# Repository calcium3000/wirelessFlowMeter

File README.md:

# wirelessFlowMeter
This project is currently in development.  Check back soon!  But not too soon.

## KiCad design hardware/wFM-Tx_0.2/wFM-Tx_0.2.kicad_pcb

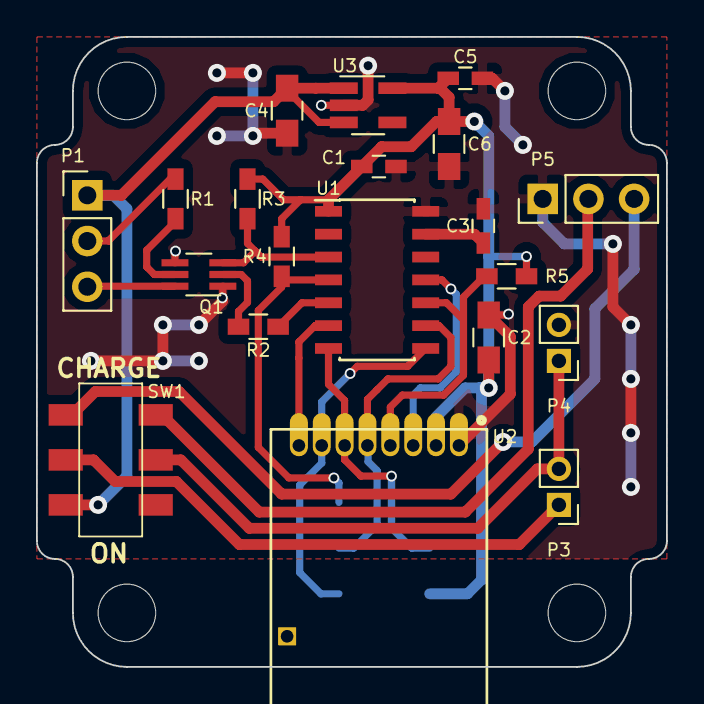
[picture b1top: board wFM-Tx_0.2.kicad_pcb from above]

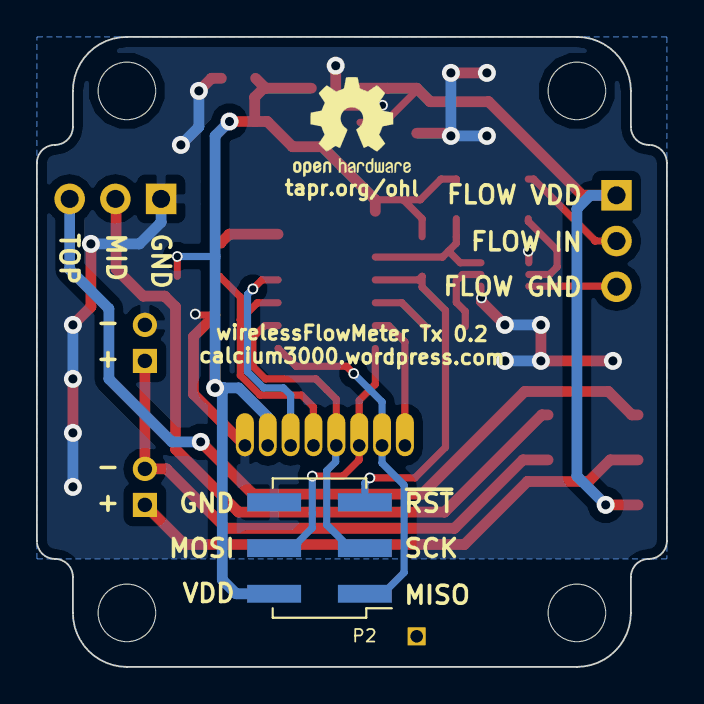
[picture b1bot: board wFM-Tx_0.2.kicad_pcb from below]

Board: 2 copper layers, 35.0 x 35.0 mm, 26 parts (2 on the bottom side), 21 nets.

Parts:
C1, C3, C5: 0.1uF; C_0603_HandSoldering
C2, C4, C6: 4.7uF; C_0805_HandSoldering
MH0, MH1, MH2, MH3: MountingHole_3.2mm_M3_ISO7380
P1, P5: 1x3; Socket_Strip_Straight_1x03_Pitch2.54mm
P2: 2x3; Socket_Strip_Straight_2x03_Pitch2.54mm_SMD
P3, P4: 1x2; S2B-PH-K-S
Q1: MBT3904DW1T1G; SOT-363_SC-70-6_Handsoldering
R1, R2, R3, R4, R5: 10k; R_0603_HandSoldering
SW1: CL-SB-22B-11T; CL-SB-12B-11T_DPDT
SYM0: OSHW-Logo2_7.3x6mm_SilkScreen
U1: ATtiny441-SSU; SOIC-14_3.9x8.7mm_Pitch1.27mm
U2: nRF24L01+_module; nRF24L01p_mini_TH
U3: MIC5205-3.0; SOT-23-5_HandSoldering

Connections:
+VDD: C1.1, C2.1, C5.1, C6.1, P2.2, R3.1, R4.1, R5.1, U1.1, U2.2, U3.5
/FLOW_GND_BASE: Q1.2, R2.1
/FLOW_IN_BASE: Q1.5, R1.1
/TINY_AREF: C3.1, U1.13
BATT_MID: P3.2, P4.1, SW1.5
BATT_POS: P3.1, SW1.2
CHRG_MID: P5.2, SW1.4
CHRG_POS: P5.3, SW1.1
FLOW_GND: P1.3, Q1.6
FLOW_GND_BR: R2.2, U1.5
FLOW_IN_BR: P1.2, R1.2
FLOW_PULSE: Q1.3, R3.2, U1.3
GND: C1.2, C2.2, C3.2, C4.2, C5.2, C6.2, P2.6, P4.2, P5.1, Q1.1, Q1.4, U1.14, U2.1, U3.2
NRF_CE: U1.11, U2.3
NRF_~CS: R5.2, U1.10, U2.4
NRF_~IRQ: U1.6, U2.8
SPI_MISO: P2.1, U1.8, U2.7
SPI_MOSI: P2.4, U1.7, U2.6
SPI_SCK: P2.3, U1.9, U2.5
TINY_~RST: P2.5, R4.2, U1.4
VBATT_2S: C4.1, P1.1, SW1.3, U3.1, U3.3

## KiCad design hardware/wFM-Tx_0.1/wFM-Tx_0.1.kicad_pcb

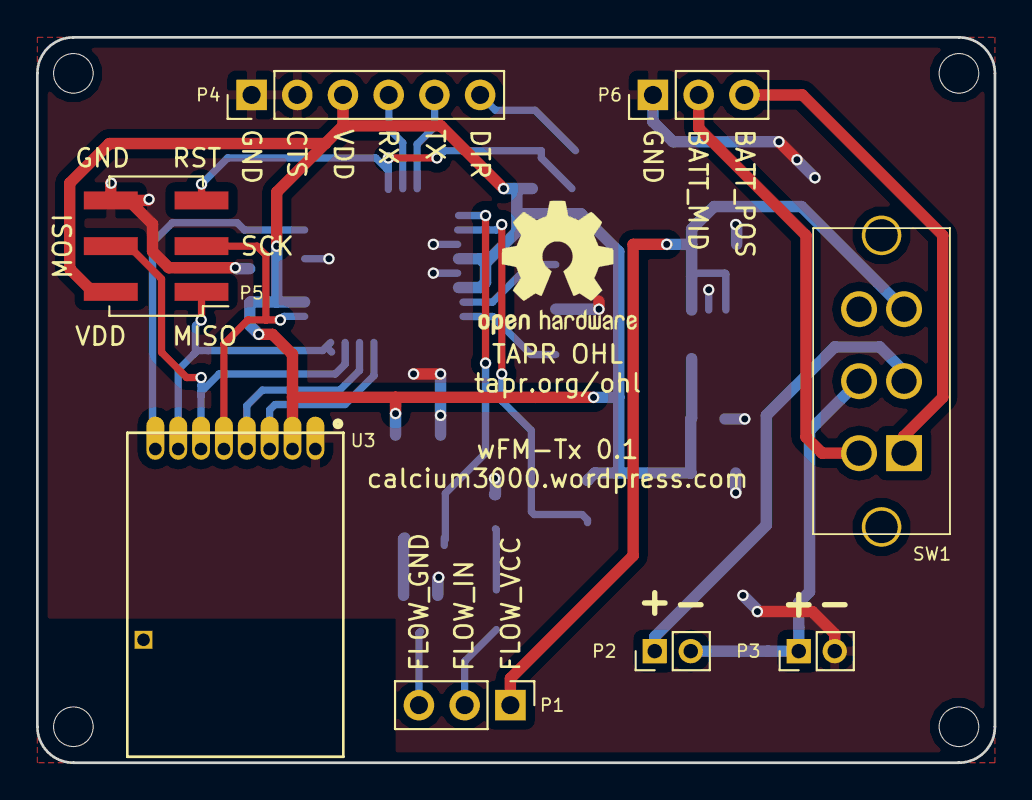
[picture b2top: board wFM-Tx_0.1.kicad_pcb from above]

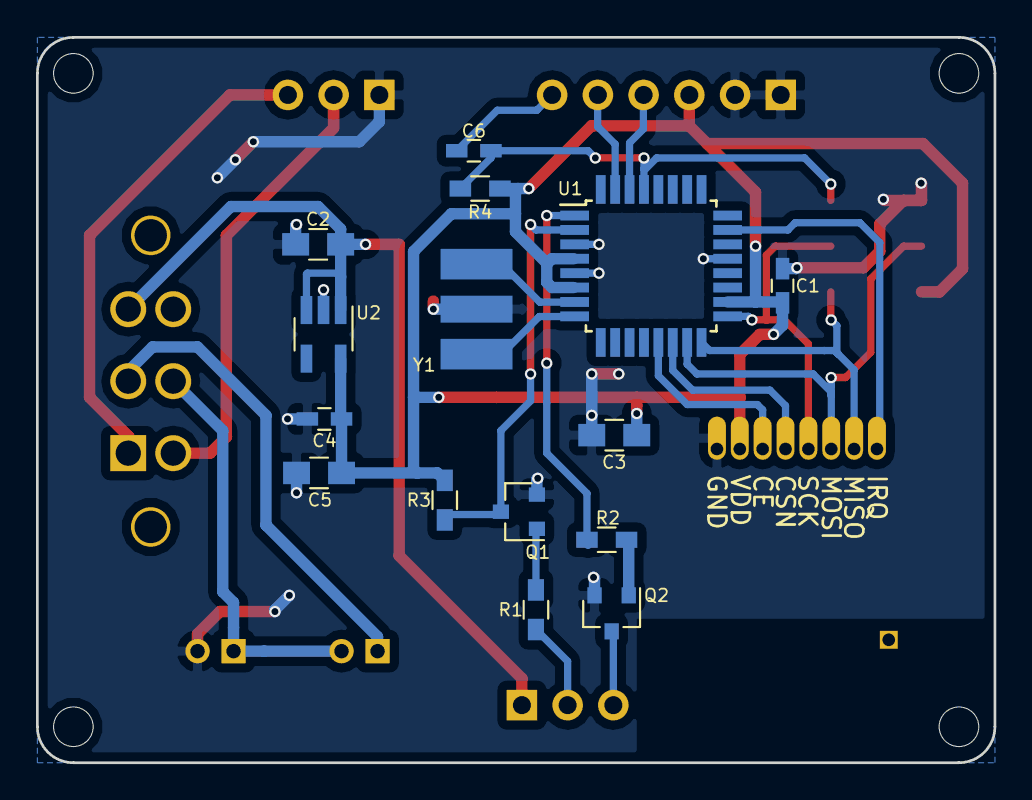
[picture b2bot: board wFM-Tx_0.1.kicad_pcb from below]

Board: 2 copper layers, 53.2 x 40.3 mm, 28 parts (15 on the bottom side), 25 nets.

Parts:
C1, C4, C6: 0.1uF; C_0603_HandSoldering
C2, C3, C5: 10uF; C_0805_HandSoldering
MH0, MH0#2, MH0#3, MH0#4: MountingHole_2.2mm_M2_ISO7380
P1, P6: 1x3; Socket_Strip_Straight_1x03_Pitch2.54mm
P2, P3: 1x2; S2B-PH-K-S
P4: 1x6; Socket_Strip_Straight_1x06_Pitch2.54mm
P5: 2x3; Socket_Strip_Straight_2x03_Pitch2.54mm_SMD
Q1, Q2: MMBT3904; SOT-23
R1, R2, R3, R4: 10k; R_0603_HandSoldering
SW1: EG2219; MFS201N-16-Z_DPDT
SYM0: OSHW-Logo2_9.8x8mm_SilkScreen
U1: ATmega328P-AU; TQFP-32_7x7mm_Pitch0.8mm
U2: MIC5205-3.3; SOT-23-5_HandSoldering
U3: nRF24L01+_module; nRF24L01p_mini_TH
Y1: PBRC8.00HR50X000; Resonator_PBRC_H

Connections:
+VDD: C1.1, C3.1, C4.1, C5.1, P4.3, P5.2, R3.1, R4.1, U1.4, U1.6, U1.18, U2.5, U3.2
/FLOW_GND_BASE: Q2.1, R2.1
/FLOW_IN_BASE: Q1.1, R1.1
/RES1: U1.7, Y1.3
/RES2: U1.8, Y1.1
BATT_MID: P2.2, P3.1, SW1.5
BATT_POS: P2.1, SW1.2
CHRG_MID: P6.2, SW1.4
CHRG_POS: P6.3, SW1.1
FLOW_GND: P1.3, Q2.3
FLOW_GND_BR: R2.2, U1.1
FLOW_IN_BR: P1.2, R1.2
FLOW_PULSE: Q1.3, R3.2, U1.2
GND: C1.2, C2.2, C3.2, C4.2, C5.2, P3.2, P4.1, P4.2, P5.6, P6.1, Q1.2, Q2.2, U1.3, U1.5, U1.21, U2.2, U3.1, Y1.2
NRF_CE: U1.13, U3.3
NRF_~CS: U1.14, U3.4
NRF_~IRQ: U1.23, U3.8
PROG_DTR: C6.1, P4.6
PROG_RX: P4.4, U1.30
PROG_TX: P4.5, U1.31
PROG_~RST: C6.2, P5.5, R4.2, U1.29
SPI_MISO: P5.1, U1.16, U3.7
SPI_MOSI: P5.4, U1.15, U3.6
SPI_SCK: P5.3, U1.17, U3.5
VBATT_2S: C2.1, P1.1, SW1.3, U2.1, U2.3

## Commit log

2017-09-28 Initial commit of hardware and software files
2017-09-29 Added silkscreen text on PCB, updated gerbers
2017-10-14 Updated Tx to version 0.2, exchanging ATmega328p for ATtiny441
